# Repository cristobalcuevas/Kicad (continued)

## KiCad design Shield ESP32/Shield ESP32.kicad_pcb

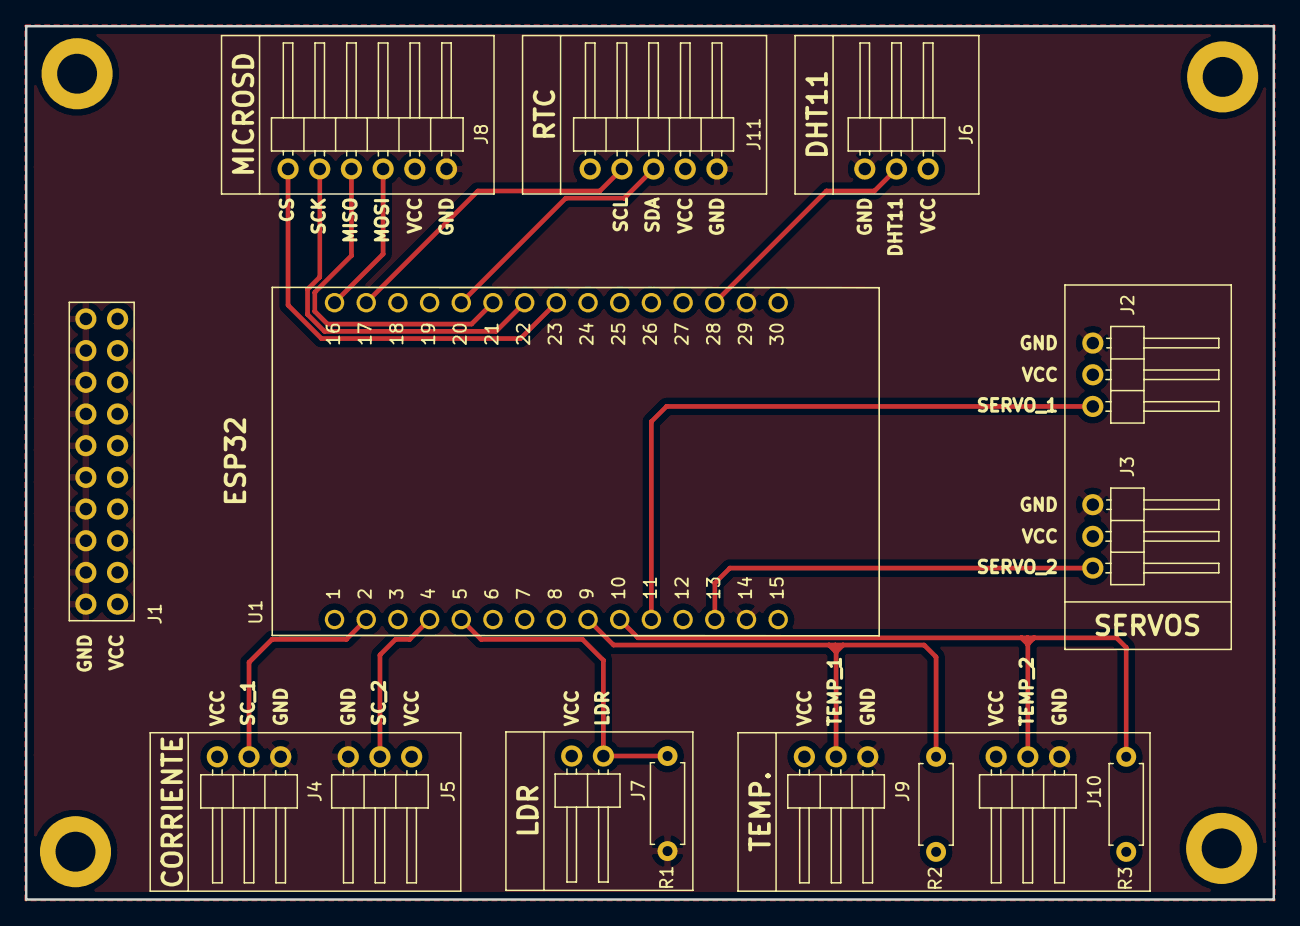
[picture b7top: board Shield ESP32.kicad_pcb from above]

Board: 2 copper layers, 100.0 x 70.0 mm, 19 parts (0 on the bottom side), 16 nets.

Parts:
H1, H2, H3, H4: MountingHole; MountingHole_3.2mm_M3_ISO7380_Pad
J1: CONECTORES; PinHeader_2x10_P2.54mm_Vertical
J2: SERVO_1; PinHeader_1x03_P2.54mm_Horizontal
J3: SERVO_2; PinHeader_1x03_P2.54mm_Horizontal
J4: SC_1; PinHeader_1x03_P2.54mm_Horizontal
J5: SC_2; PinHeader_1x03_P2.54mm_Horizontal
J6: DHT11; PinHeader_1x03_P2.54mm_Horizontal
J7: LDR; PinHeader_1x02_P2.54mm_Horizontal
J8: SD; PinHeader_1x06_P2.54mm_Horizontal
J9: DS18B20_1; PinHeader_1x03_P2.54mm_Horizontal
J10: DS18B20_2; PinHeader_1x03_P2.54mm_Horizontal
J11: RTC; PinHeader_1x05_P2.54mm_Horizontal
R1: 10k; R_Axial_DIN0207_L6.3mm_D2.5mm_P7.62mm_Horizontal
R2, R3: 4.7k; R_Axial_DIN0207_L6.3mm_D2.5mm_P7.62mm_Horizontal
U1: ESP32_30

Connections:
+5V: J1.1, J1.3, J1.5, J1.7, J1.9, J1.11, J1.13, J1.15, J1.17, J1.19, J2.2, J3.2, J4.1, J5.1, J6.3, J7.2, J8.5, J9.3, J10.3, J11.4, R2.1, R3.1
/Corriente/SC_1: J4.2, U1.2
/Corriente/SC_2: J5.2, U1.4
/DHT11/DHT11: J6.2, U1.28
/ESP32/CS: J8.1, U1.23
/ESP32/LDR: J7.1, R1.1, U1.5
/ESP32/MISO: J8.3, U1.21
/ESP32/MOSI: J8.4, U1.16
/ESP32/SCK: J8.2, U1.22
/ESP32/SCL: J11.2, U1.17
/ESP32/SDA: J11.3, U1.20
/ESP32/SERVO_1: J2.3, U1.11
/ESP32/SERVO_2: J3.3, U1.13
/ESP32/TEMP_1: J9.2, R2.2, U1.9
/ESP32/TEMP_2: J10.2, R3.2, U1.10
GND: J1.2, J1.4, J1.6, J1.8, J1.10, J1.12, J1.14, J1.16, J1.18, J1.20, J2.1, J3.1, J4.3, J5.3, J6.1, J8.6, J9.1, J10.1, J11.5, R1.2, U1.14, U1.29

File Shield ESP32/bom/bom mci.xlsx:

Item # | Designator | Quantity | Manufacturer | Mfg Part # | Name | Description | Value | Package/Footprint | Type
1 | R1 | 15 | STACKPOLE ELECTRONICS INC | CF14JT10K0CT-ND | RESISTOR | RESISTOR DIN0207 | 10kΩ | R_Axial_DIN0207_L6.3mm_D2.5mm_P7.62mm_Horizontal | THT
2 | R2, R3 | 30 | STACKPOLE ELECTRONICS INC | CF14JT4K70CT-ND | RESISTOR | RESISTOR DIN0207 | 4.7kΩ | R_Axial_DIN0207_L6.3mm_D2.5mm_P7.62mm_Horizontal | THT
3 | J1 | 8 | MCI | MCI07806 | CONECTORES | PIN HEADER 2X40 VERTICAL DOBLE | - | PinHeader_2x40_P2.54mm_Vertical | THT
4 | J2, J3, J4, J5, J6, J7, J8, J9, J10, J11 | 15 | MCI | MCI00178 | LDR, SERVO_1, SERVO_2, SC_1, SC_2, DHT11, DS18B20_1, DS18B20_2, RTC, SD | PIN HEADER 1X40 ÁNGULO 90° | - | PinHeader_1x40_P2.54mm_Horizontal | THT
